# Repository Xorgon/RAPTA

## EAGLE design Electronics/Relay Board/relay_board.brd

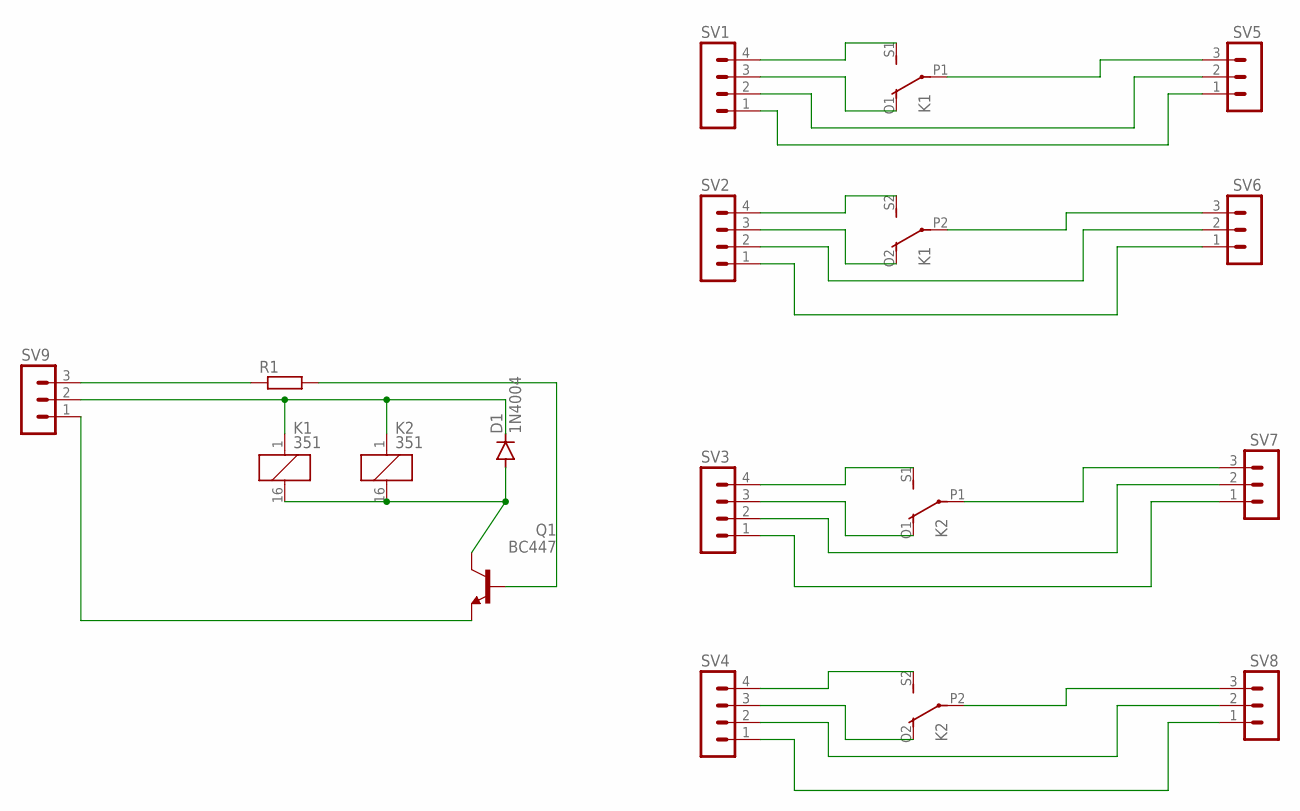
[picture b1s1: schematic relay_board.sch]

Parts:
D1: 1N4004; DO41-10
K1, K2: 351
Q1: BC447; TO92-EBC
R1: R-EU_0207/15; 0207/15
SV1, SV2, SV3, SV4: MA04-1
SV5, SV6, SV7, SV8, SV9: MA03-1

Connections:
unnamed: K1.O1 (O), SV1.3
unnamed: K1.S1 (S), SV1.4
unnamed: K1.S2 (S), SV2.4
unnamed: K1.O2 (O), SV2.3
unnamed: K2.S1 (S), SV3.4
unnamed: K2.O1 (O), SV3.3
unnamed: K2.S2 (S), SV4.4
unnamed: K2.O2 (O), SV4.3
unnamed: K1.P1, SV5.3
unnamed: SV1.1, SV5.1
unnamed: SV1.2, SV5.2
unnamed: K1.P2, SV6.3
unnamed: SV2.2, SV6.2
unnamed: SV2.1, SV6.1
unnamed: K2.P1, SV7.3
unnamed: K2.P2, SV8.3
unnamed: SV3.2, SV7.2
unnamed: SV3.1, SV7.1
unnamed: SV4.2, SV8.2
unnamed: SV4.1, SV8.1
unnamed: D1.C, K1.1, K2.1, SV9.2
unnamed: D1.A, K1.16 (2), K2.16 (2), Q1.C
unnamed: Q1.E, SV9.1
unnamed: R1.1, SV9.3
unnamed: Q1.B, R1.2

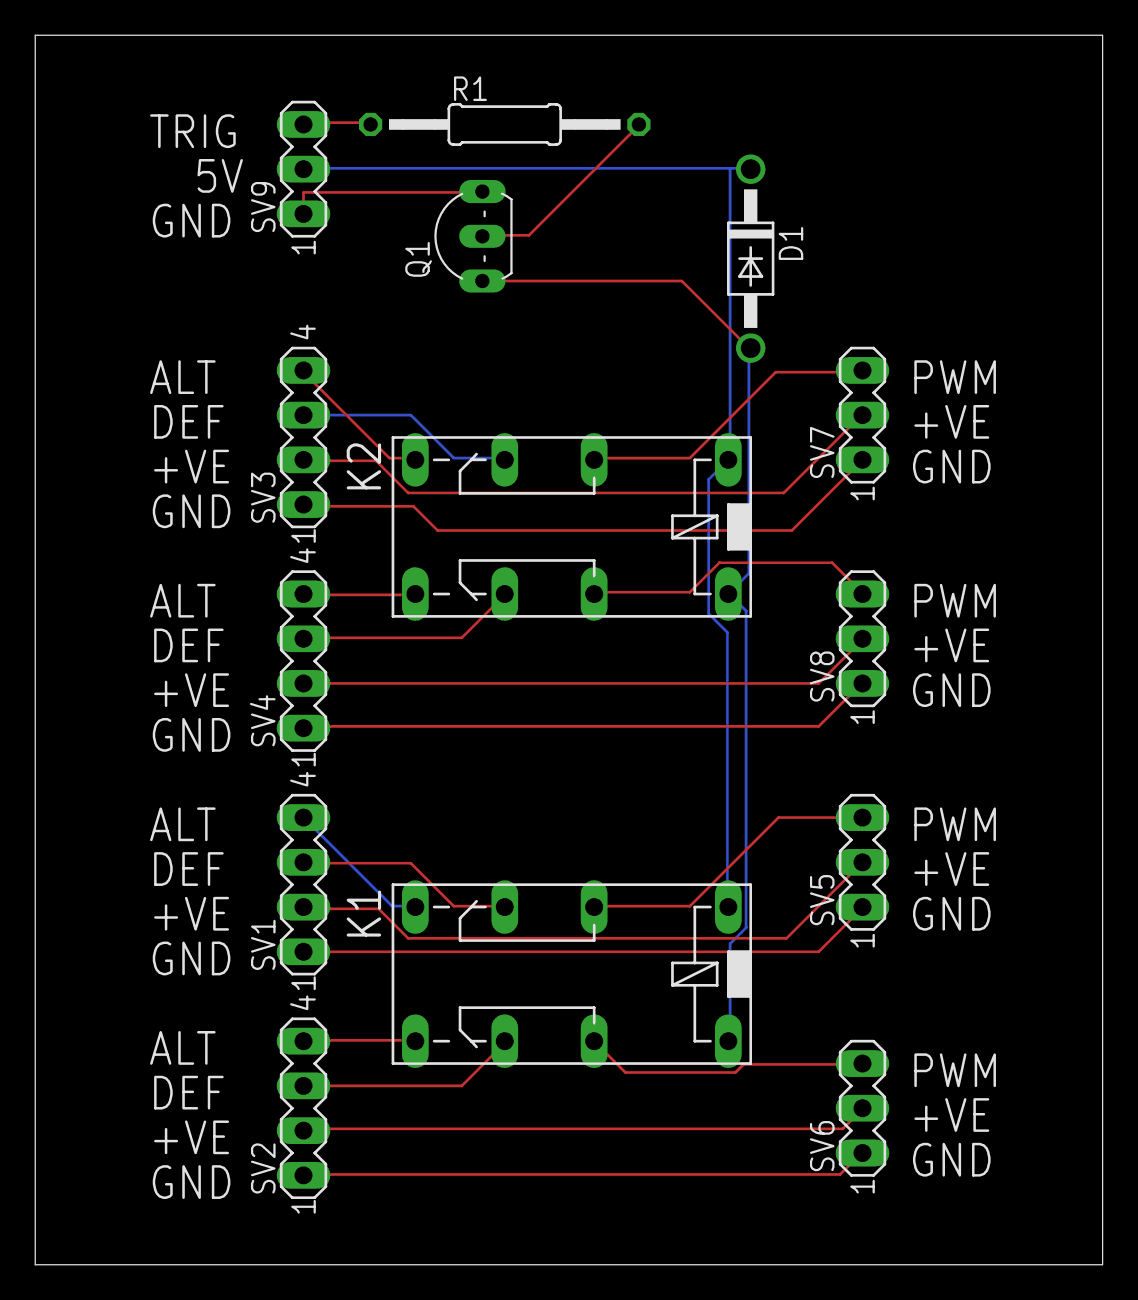
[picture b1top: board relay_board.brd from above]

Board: 2 copper layers, 60.6 x 69.8 mm, 14 parts (0 on the bottom side), 25 nets.

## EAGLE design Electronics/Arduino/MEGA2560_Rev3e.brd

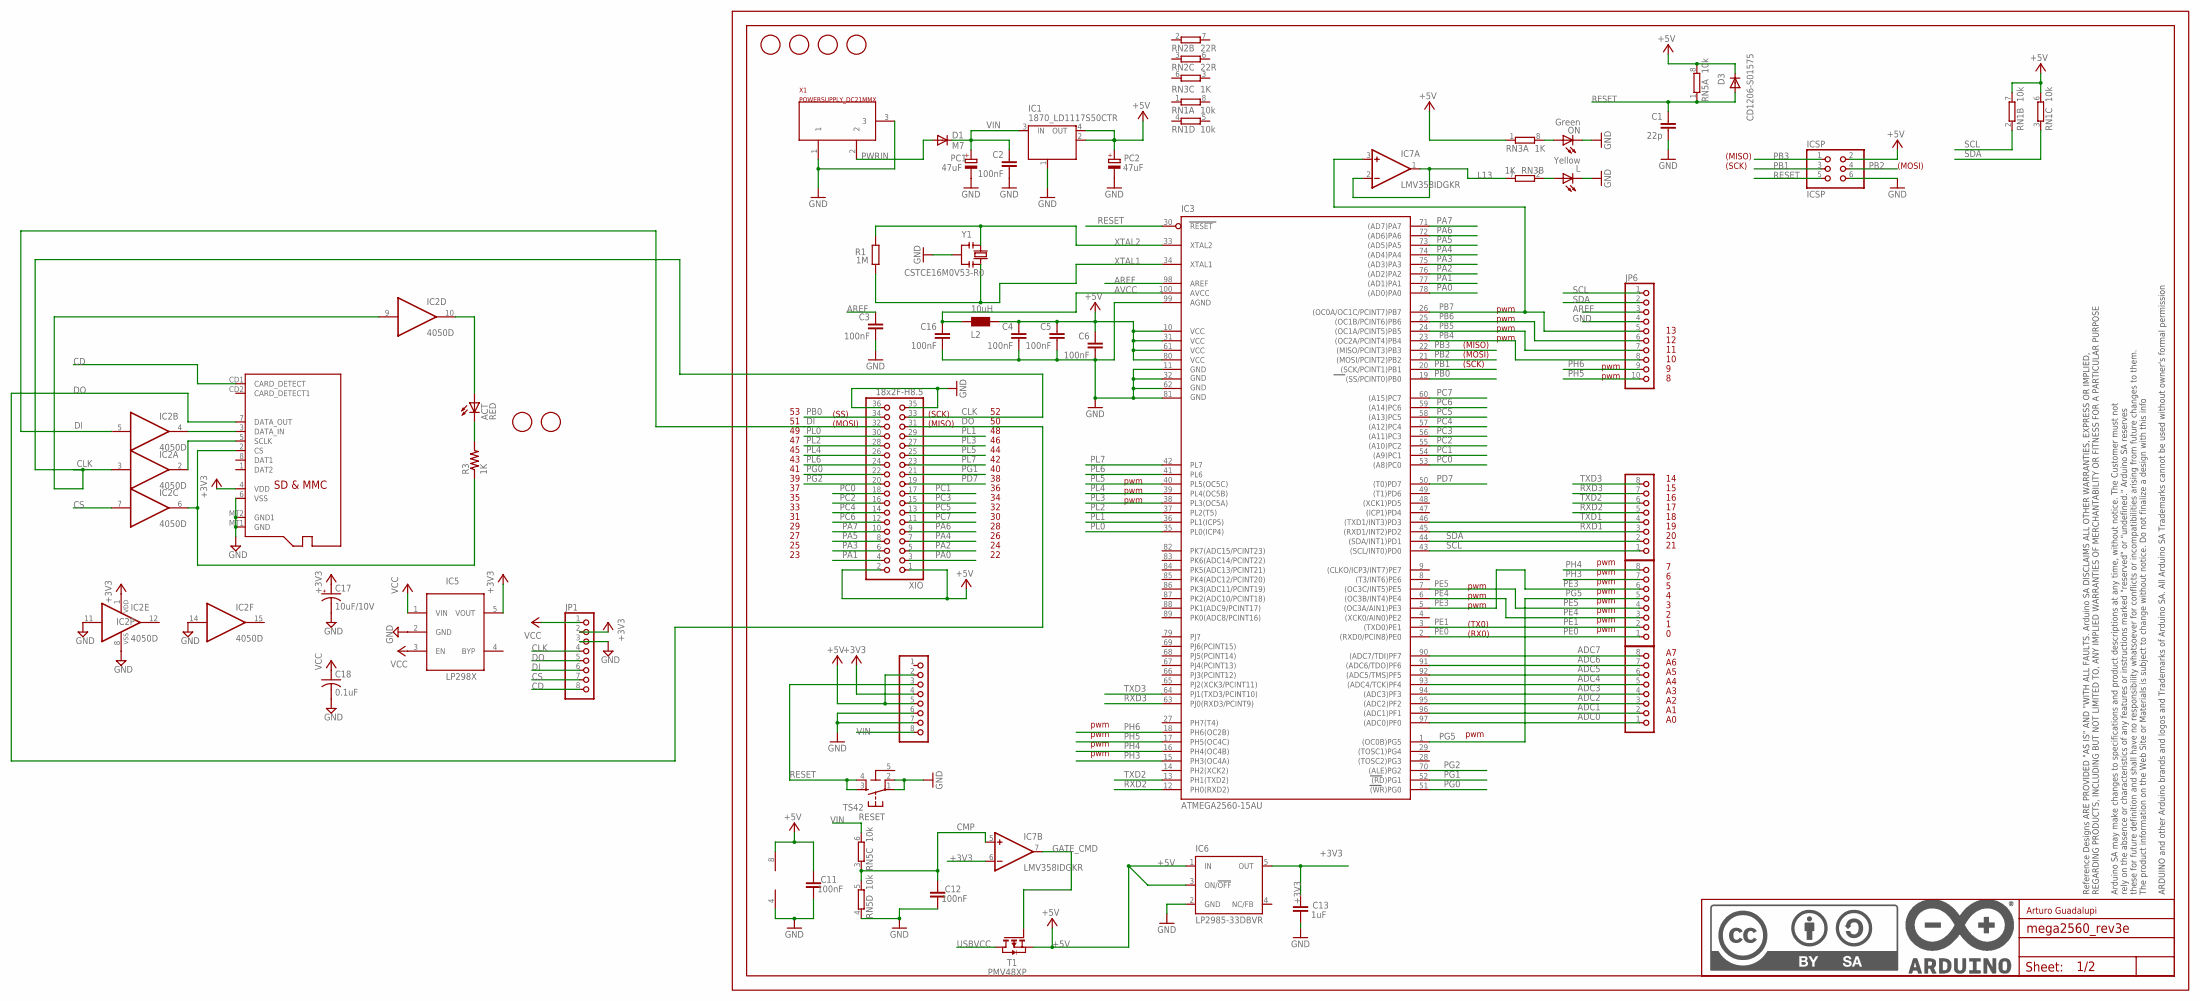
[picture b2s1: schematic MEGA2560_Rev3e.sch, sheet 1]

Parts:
ACT: RED; CHIP-LED0805
ADCL: FH254-108DF08500V; 1X08
C1: 22p; C0603-ROUND
C2, C3, C4, C5, C6, C11, C12, C16: 100nF; C0603-ROUND
C13: 1uF; C0603-ROUND
C17: 10uF/10V; A/3216-18R
C18: 0.1uF; C0805K
COMMUNICATION: FH254-108DF08500V; 1X08
D1: M7; SMB
D3: CD1206-S01575; MINIMELF
FD1, FD2, FD3, FD4: FIDUCIALMOUNT; FIDUCIA-MOUNT
IC1: 1870_LD1117S50CTR; LINEAR_SOT223
IC2: 4050D; SO16
IC3: ATMEGA2560-15AU; TQFP100
IC5: LP298XS; SOT23-5L
IC6: LP2985-33DBVR; SOT23-DBV
IC7: LMV358IDGKR; MSOP08
ICSP: ICSP; 2X03
JP1: PINHD-1X8BIG; 1X08-BIG
JP6: FH254-110DF08500V; 1X10
L: Yellow; CHIPLED_0805
L2: 10uH; 0805
ON: Green; CHIPLED_0805
PC1, PC2: 47uF; PANASONIC_D
POWER: FH254-108DF08500V; 1X08
PWML: FH254-108DF08500V; 1X08
R1: 1M; R0603-ROUND
R3: 1K; R0805
RESET: TS42
RN1, RN5: 10k; CAY16
RN2: 22R; CAY16
RN3: 1K; CAY16
T1: PMV48XP; SOT-23; PART_NUMBER PMV48XP
U$1: DNP; FRAME
U$3, U$4: FIDUCIAL; FIDUCIAL_1MM
X1: POWERSUPPLY_DC21MMX; POWERSUPPLY_DC-21MM
X3: MICROSD
XIO: 18x2F-H8.5; 2X18
Y1: CSTCE16M0V53-R0; RESONATOR

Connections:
5-GND: RESET.5 (5-GND)
+3V3: C13.2, C17.+, IC2.1 (VDD), IC5.5 (VOUT), IC6.5 (OUT), IC7.6 (-IN), JP1.2, POWER.4, X3.4 (VDD)
+5V: C4.1, C5.1, C6.1, C11.2, D3.C, IC1.2 (OUT), IC1.4 (OUT), IC3.10 (VCC), IC3.31 (VCC1), IC3.61 (VCC2), IC3.80 (VCC3), IC6.1 (IN), IC6.3 (ON/!OFF), IC7.8 (V+), ICSP.2, L2.2, PC2.+, POWER.2, POWER.5, RN1.6 (2), RN1.7 (2), RN3.1, RN5.8 (2), T1.2 (S), XIO.1, XIO.2; also elsewhere on the board
ADC0: ADCL.1, IC3.97 ((ADC0)PF0)
ADC1: ADCL.2, IC3.96 ((ADC1)PF1)
ADC2: ADCL.3, IC3.95 ((ADC2)PF2)
ADC3: ADCL.4, IC3.94 ((ADC3)PF3)
ADC4: ADCL.5, IC3.93 ((ADC4/TCK)PF4)
ADC5: ADCL.6, IC3.92 ((ADC5/TMS)PF5)
ADC6: ADCL.7, IC3.91 ((ADC6/TDO)PF6)
ADC7: ADCL.8, IC3.90 ((ADC7/TDI)PF7)
AREF: C3.1, IC3.98 (AREF), JP6.3
AVCC: C16.1, IC3.100 (AVCC), L2.1
CD: JP1.8, X3.CD1 (CARD_DETECT)
CLK: IC2.3 (I), IC2.9 (I), JP1.4, XIO.33
CMP: C12.2, IC7.5 (+IN), RN5.3 (1), RN5.5 (2)
CS: IC2.7 (I), JP1.7
DI: IC2.5 (I), JP1.6, XIO.32
DO: JP1.5, X3.7 (DATA_OUT), XIO.31
GATE_CMD: IC7.7 (OUT), T1.3 (G)
GND: C1.2, C2.2, C3.2, C4.2, C5.2, C6.2, C11.1, C12.1, C13.1, C16.2, C17.-, C18.2, IC1.1 (GND/ADJ), IC2.8 (VSS), IC2.11 (I), IC2.14 (I), IC3.11 (GND), IC3.32 (GND1), IC3.62 (GND2), IC3.81 (GND3), IC3.99 (AGND), IC5.2 (GND), IC6.2 (GND), IC7.4 (V-), ICSP.6, JP1.3, JP6.4, L.C, ON.C, PC1.-, PC2.-, POWER.6, POWER.7, RESET.1, RESET.2, RN5.4 (1), X1.1, X1.3, X3.6 (VSS), X3.MT1 (GND), X3.MT2 (GND1), XIO.35, XIO.36, Y1.2; also elsewhere on the board
L13: IC7.1 (OUT), IC7.2 (-IN), RN3.7 (2)
unnamed: ACT.A, IC2.10 (O)
unnamed: L.A, RN3.2 (1)
unnamed: ON.A, RN3.8 (2)
unnamed: IC2.2 (O), X3.5 (SCLK)
unnamed: IC2.6 (O), R3.1, X3.2 (CS)
unnamed: ACT.C, R3.2
unnamed: IC2.4 (O), X3.3 (DATA_IN)
PA0: IC3.78 ((AD0)PA0), XIO.3
PA1: IC3.77 ((AD1)PA1), XIO.4
PA2: IC3.76 ((AD2)PA2), XIO.5
PA3: IC3.75 ((AD3)PA3), XIO.6
PA4: IC3.74 ((AD4)PA4), XIO.7
PA5: IC3.73 ((AD5)PA5), XIO.8
PA6: IC3.72 ((AD6)PA6), XIO.9
PA7: IC3.71 ((AD7)PA7), XIO.10
PB0: IC3.19 ((SS/PCINT0)PB0), XIO.34
PB1: IC3.20 ((SCK/PCINT1)PB1), ICSP.3
PB2: IC3.21 ((MOSI/PCINT2)PB2), ICSP.4
PB3: IC3.22 ((MISO/PCINT3)PB3), ICSP.1
PB4: IC3.23 ((OC2A/PCINT4)PB4), JP6.8
PB5: IC3.24 ((OC1A/PCINT5)PB5), JP6.7
PB6: IC3.25 ((OC1B/PCINT6)PB6), JP6.6
PB7: IC3.26 ((OC0A/OC1C/PCINT7)PB7), IC7.3 (+IN), JP6.5
PC0: IC3.53 ((A8)PC0), XIO.18
PC1: IC3.54 ((A9)PC1), XIO.17
PC2: IC3.55 ((A10)PC2), XIO.16
PC3: IC3.56 ((A11)PC3), XIO.15
PC4: IC3.57 ((A12)PC4), XIO.14
PC5: IC3.58 ((A13)PC5), XIO.13
PC6: IC3.59 ((A14)PC6), XIO.12
PC7: IC3.60 ((A15)PC7), XIO.11
PD7: IC3.50 ((T0)PD7), XIO.19
PE0: IC3.2 ((RXD0/PCIN8)PE0), PWML.1; also elsewhere on the board
PE1: IC3.3 ((TXD0)PE1), PWML.2; also elsewhere on the board
PE3: IC3.5 ((OC3A/AIN1)PE3), PWML.6
PE4: IC3.6 ((OC3B/INT4)PE4), PWML.3
PE5: IC3.7 ((OC3C/INT5)PE5), PWML.4
PG0: IC3.51 ((WR)PG0), XIO.22
PG1: IC3.52 ((RD)PG1), XIO.21
PG2: IC3.70 ((ALE)PG2), XIO.20
PG5: IC3.1 ((OC0B)PG5), PWML.5
PH3: IC3.15 (PH3(OC4A)), PWML.7
PH4: IC3.16 (PH4(OC4B)), PWML.8
PH5: IC3.17 (PH5(OC4C)), JP6.10
PH6: IC3.18 (PH6(OC2B)), JP6.9
PL0: IC3.35 (PL0(ICP4)), XIO.30
PL1: IC3.36 (PL1(ICP5)), XIO.29
PL2: IC3.37 (PL2(T5)), XIO.28
PL3: IC3.38 (PL3(OC5A)), XIO.27
PL4: IC3.39 (PL4(OC5B)), XIO.26
PL5: IC3.40 (PL5(OC5C)), XIO.25
PL6: IC3.41 (PL6), XIO.24
PL7: IC3.42 (PL7), XIO.23
PWRIN: D1.A, X1.2
RESET: C1.1, D3.A, IC3.30 (RESET), ICSP.5, POWER.3, RESET.3, RESET.4, RN5.1; also elsewhere on the board
RXD1: COMMUNICATION.3, IC3.45 ((RXD1/INT2)PD2)
RXD2: COMMUNICATION.5, IC3.12 (PH0(RXD2))
RXD3: COMMUNICATION.7, IC3.63 (PJ0(RXD3/PCINT9))
SCL: COMMUNICATION.1, IC3.43 ((SCL/INT0)PD0), JP6.1, RN1.2 (1)
SDA: COMMUNICATION.2, IC3.44 ((SDA/INT1)PD1), JP6.2, RN1.3 (1)
TXD1: COMMUNICATION.4, IC3.46 ((TXD1/INT3)PD3)
TXD2: COMMUNICATION.6, IC3.13 (PH1(TXD2))
TXD3: COMMUNICATION.8, IC3.64 (PJ1(TXD3/PCINT10))
USBVCC: T1.1 (D); also elsewhere on the board
VCC: C18.1, IC5.1 (VIN), IC5.3 (EN), JP1.1
VIN: C2.1, D1.C, IC1.3 (IN), PC1.+, POWER.8, RN5.6 (2)
XTAL1: IC3.34 (XTAL1), R1.1, Y1.3
XTAL2: IC3.33 (XTAL2), R1.2, Y1.1

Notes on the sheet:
(SCK)
(MISO)
(MOSI)
pwm
(TX0)
(RX0)
(SS)
Arturo Guadalupi

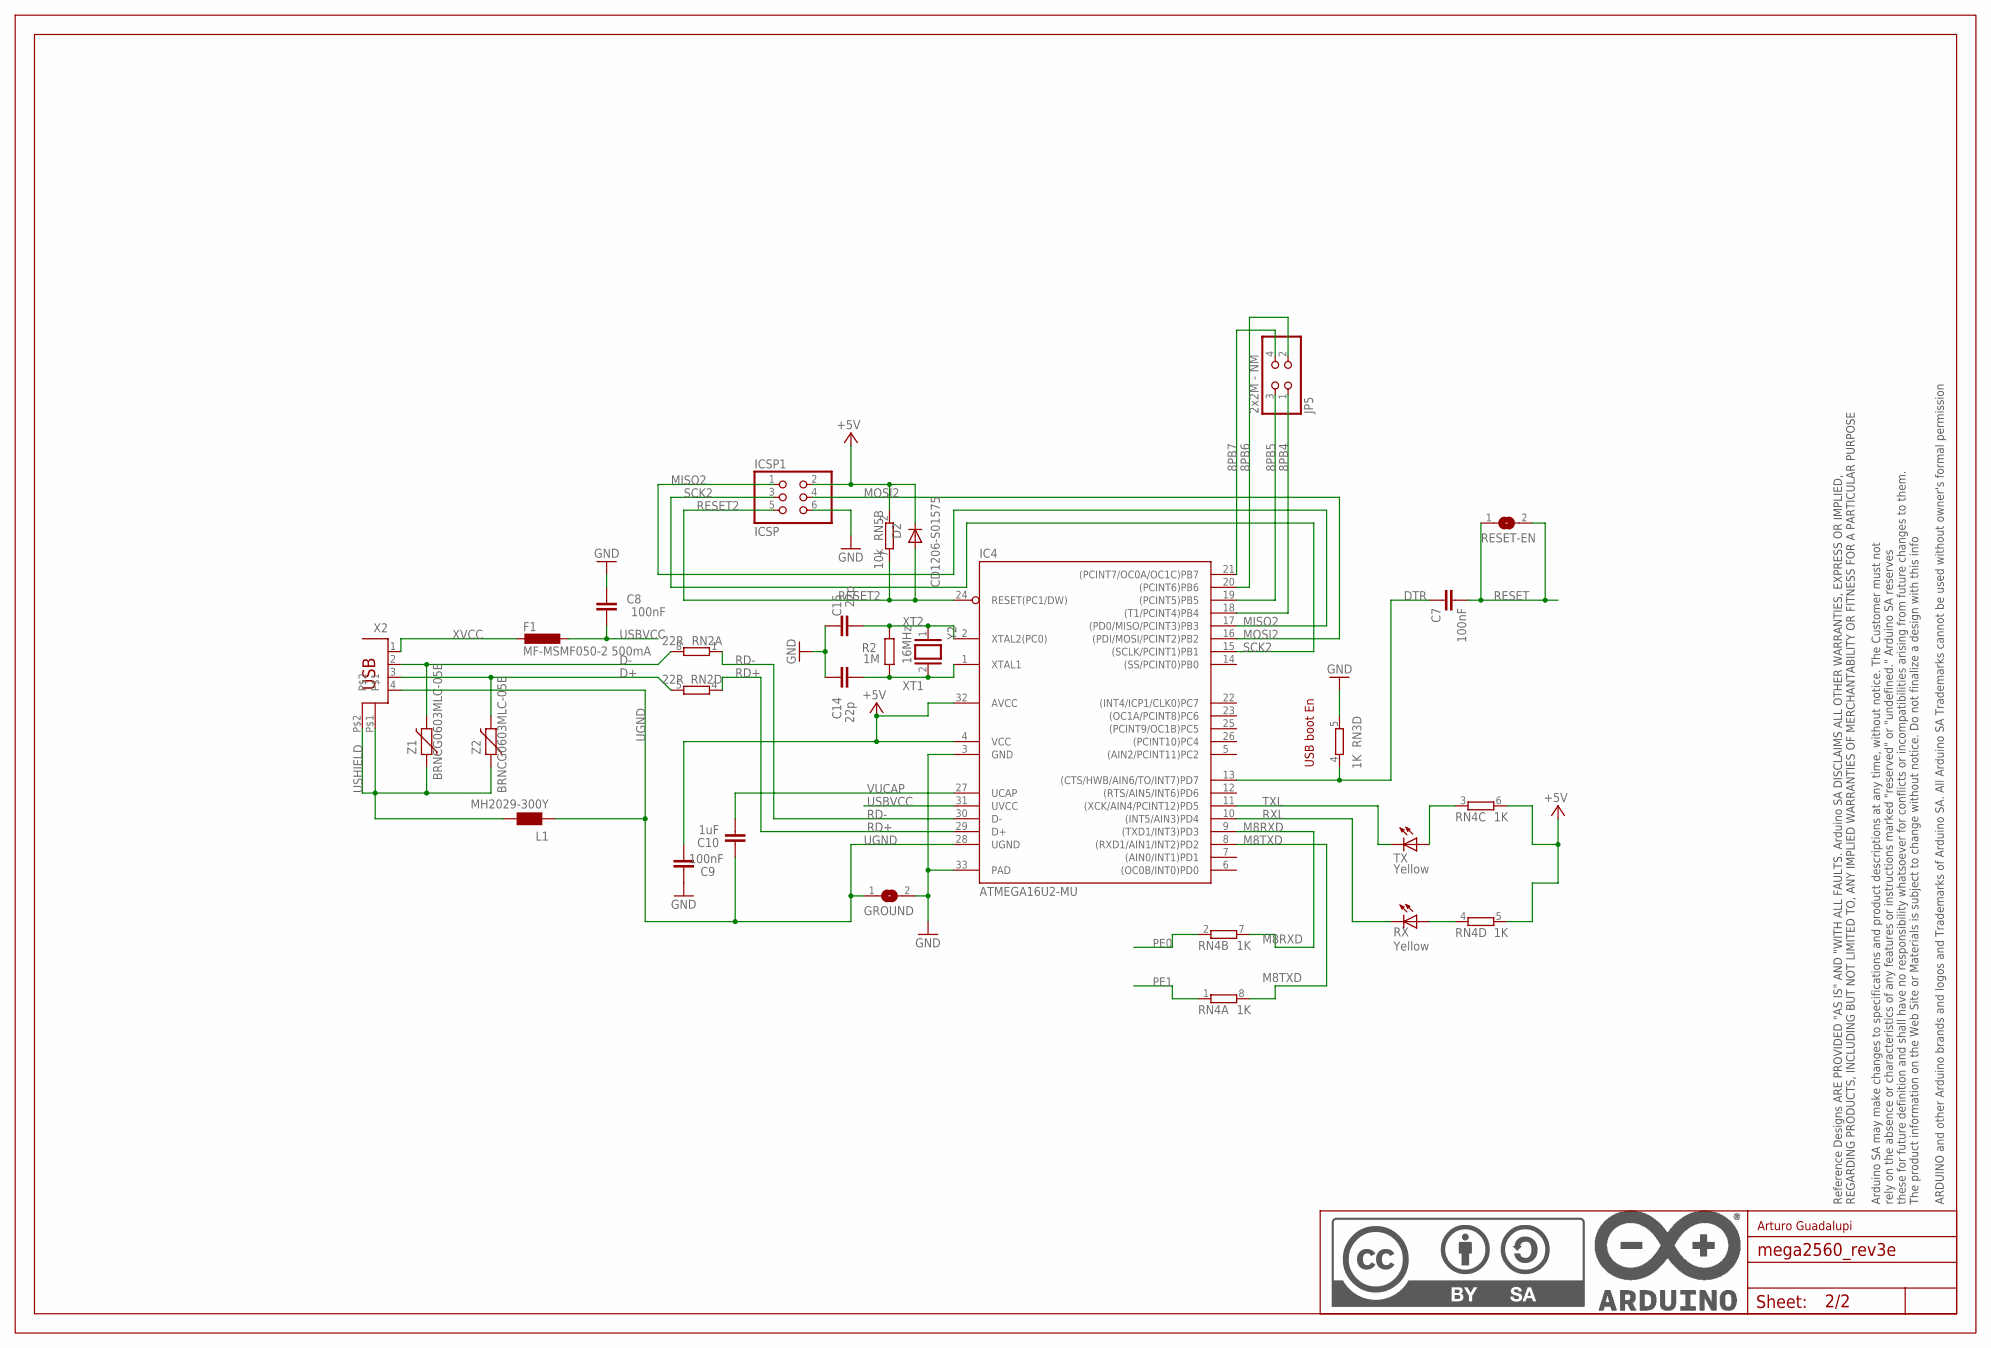
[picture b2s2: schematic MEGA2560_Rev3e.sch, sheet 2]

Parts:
C7, C8, C9: 100nF; C0603-ROUND
C10: 1uF; C0603-ROUND
C14, C15: 22p; C0603-ROUND
D2: CD1206-S01575; MINIMELF
F1: MF-MSMF050-2 500mA; L1812
GROUND: SJ
IC4: ATMEGA16U2-MU; MLF32
ICSP1: ICSP; 2X03
JP5: 2x2M - NM; 2X02
L1: MH2029-300Y; 0805
R2: 1M; R0603-ROUND
RESET-EN: SJ
RN2: 22R; CAY16
RN3, RN4: 1K; CAY16
RN5: 10k; CAY16
RX: Yellow; CHIPLED_0805
TX: Yellow; CHIPLED_0805
U$2: DNP; FRAME
X2: 0056_USB-B-S-RA-WT-SPCC; PN61729
Y2: 16MHz; QS
Z1, Z2: BRNCG0603MLC-05E; CT/CN0603

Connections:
8PB4: IC4.18 ((T1/PCINT4)PB4), JP5.1
8PB5: IC4.19 ((PCINT5)PB5), JP5.3
8PB6: IC4.20 ((PCINT6)PB6), JP5.2
8PB7: IC4.21 ((PCINT7/OC0A/OC1C)PB7), JP5.4
+5V: C9.1, D2.C, IC4.4 (VCC), IC4.32 (AVCC), ICSP1.2, RN4.5 (2), RN4.6 (2), RN5.2 (1); also elsewhere on the board
D+: RN2.5 (2), X2.3, Z2.2
D-: RN2.8 (2), X2.2, Z1.2
DTR: C7.1, IC4.13 ((CTS/HWB/AIN6/TO/INT7)PD7), RN3.4 (1)
GND: C8.2, C9.2, C14.2, C15.2, GROUND.2, IC4.3 (GND), IC4.33 (PAD), ICSP1.6, RN3.5 (2); also elsewhere on the board
M8RXD: IC4.9 ((TXD1/INT3)PD3), RN4.7 (2)
M8TXD: IC4.8 ((RXD1/AIN1/INT2)PD2), RN4.8 (2)
MISO2: IC4.17 ((PD0/MISO/PCINT3)PB3), ICSP1.1
MOSI2: IC4.16 ((PDI/MOSI/PCINT2)PB2), ICSP1.4
unnamed: RN4.4 (1), RX.A
unnamed: RN4.3 (1), TX.A
PE0: RN4.2 (1); also elsewhere on the board
PE1: RN4.1; also elsewhere on the board
RD+: IC4.29 (D+), RN2.4 (1)
RD-: IC4.30 (D-), RN2.1
RESET: C7.2, RESET-EN.1, RESET-EN.2; also elsewhere on the board
RESET2: D2.A, IC4.24 (RESET(PC1/DW)), ICSP1.5, RN5.7 (2)
RXL: IC4.10 ((INT5/AIN3)PD4), RX.C
SCK2: IC4.15 ((SCLK/PCINT1)PB1), ICSP1.3
TXL: IC4.11 ((XCK/AIN4/PCINT12)PD5), TX.C
UGND: C10.2, GROUND.1, IC4.28 (UGND), L1.1, X2.4
USBVCC: C8.1, F1.1, IC4.31 (UVCC); also elsewhere on the board
USHIELD: L1.2, X2.P$1, X2.P$2, Z1.1, Z2.1
VUCAP: C10.1, IC4.27 (UCAP)
XT1: C14.1, IC4.1 (XTAL1), R2.1, Y2.2
XT2: C15.1, IC4.2 (XTAL2(PC0)), R2.2, Y2.1
XVCC: F1.2, X2.1

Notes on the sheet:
USB boot En
Arturo Guadalupi

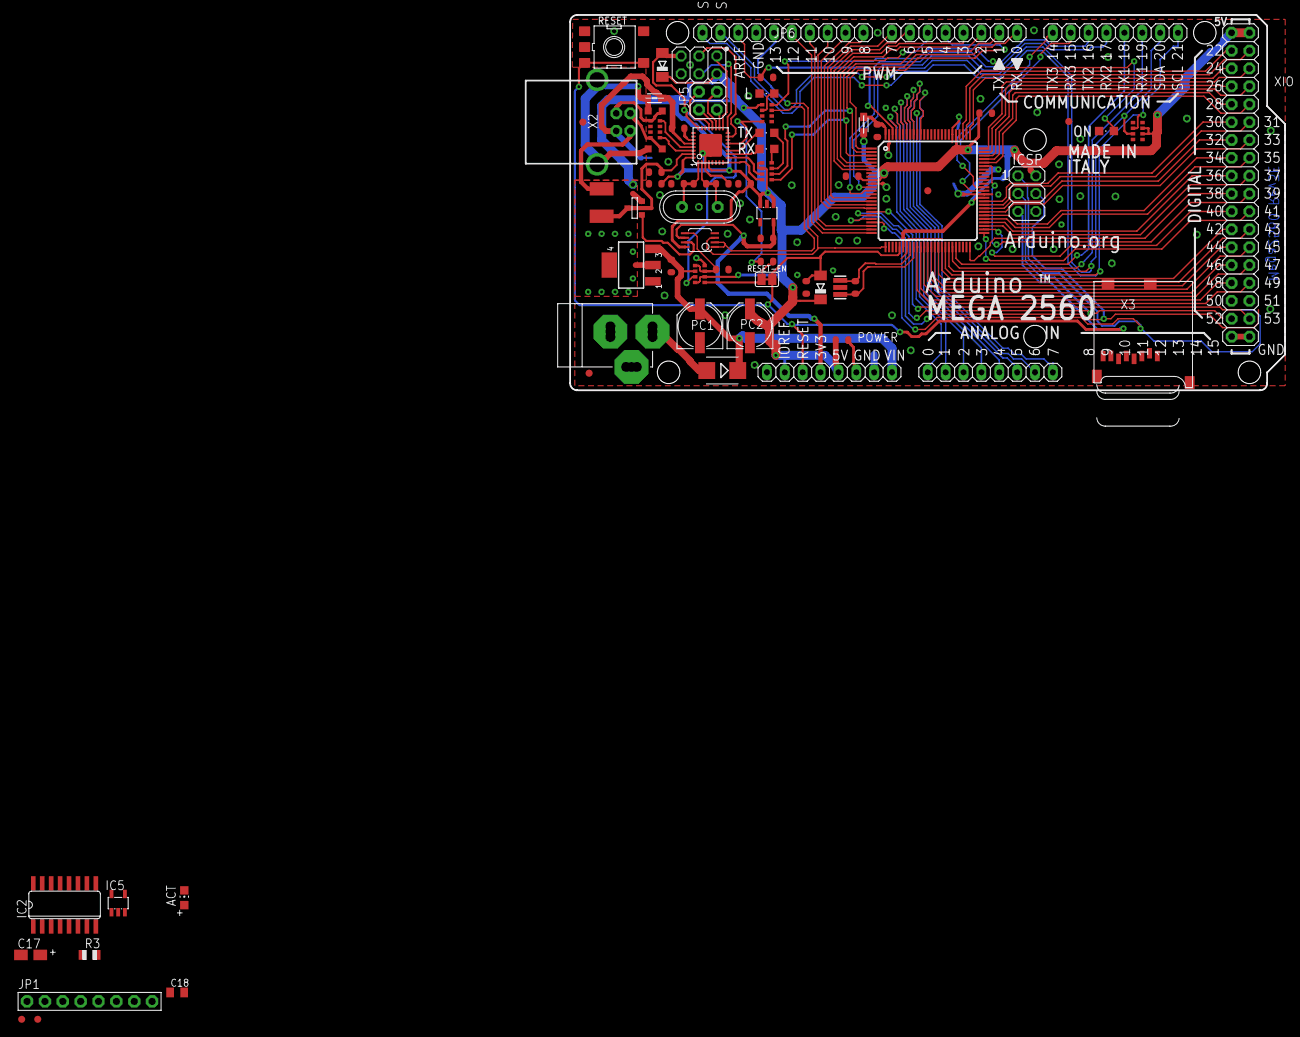
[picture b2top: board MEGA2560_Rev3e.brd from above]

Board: 2 copper layers, 101.6 x 53.3 mm, 75 parts (1 on the bottom side), 114 nets.

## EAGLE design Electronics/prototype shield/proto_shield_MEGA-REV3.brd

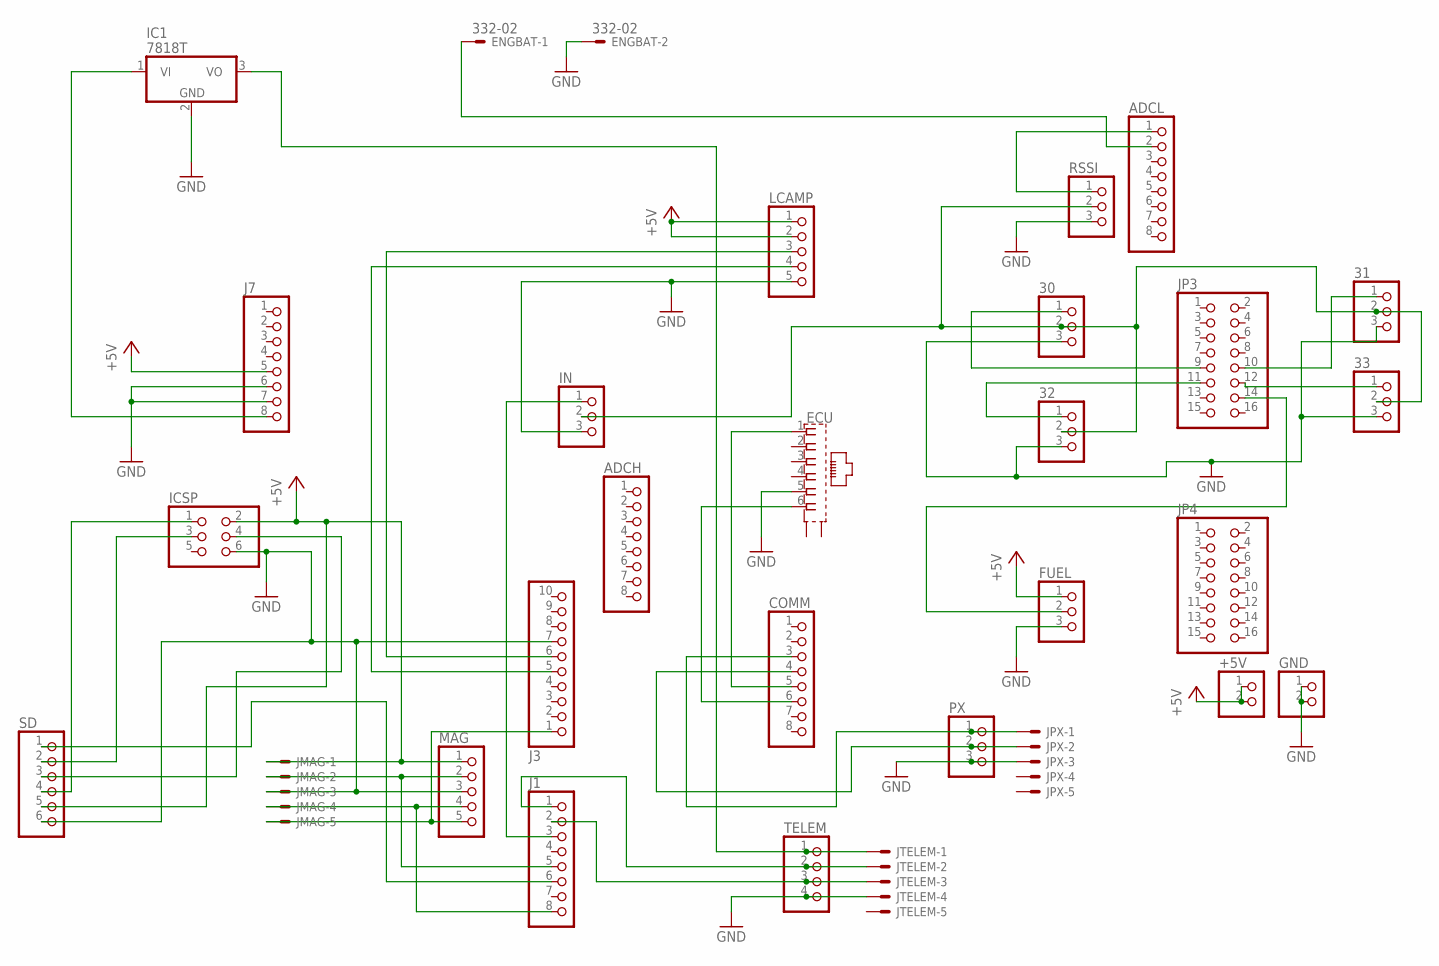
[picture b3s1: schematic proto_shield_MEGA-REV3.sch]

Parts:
30, 31, 32, 33: PINHD-1X3; 1X03
+5V: PINHD-1X2; 1X02
ADCH: PINHD-1X8TH; 1X08-TH
ADCL: PINHD-1X8TH; 1X08-TH
COMM: PINHD-1X8TH; 1X08-TH
ECU: XRJK-S-01-6-6-0-2G2-NO
ENGBAT: 332-02
FUEL: PINHD-1X3; 1X03
GND: PINHD-1X2; 1X02
IC1: 7818T; TO220H
ICSP: PINHD-2X3; 2X03
IN: PINHD-1X3; 1X03
J1, J7: PINHD-1X8TH; 1X08-TH
J3: PINHD-1X10TH; 1X10-TH
JMAG: BM05B-SRSS-TB
JP3, JP4: PINHD-2X8; 2X08
JPX: BM05B-SRSS-TB
JTELEM: BM05B-SRSS-TB
LCAMP: PINHD-1X5; 1X05
MAG: PINHD-1X5; 1X05
PX: PINHD-1X3; 1X03
RSSI: PINHD-1X3; 1X03
SD: PINHD-1X6; 1X06
TELEM: PINHD-1X4; 1X04

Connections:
+5V: +5V.1, +5V.2, FUEL.1, ICSP.2, J7.5, JMAG.1, LCAMP.1, LCAMP.2, MAG.1, SD.5
GND: 30.3, 31.3, 32.3, 33.3, ECU.5, ENGBAT.2, FUEL.3, GND.1, GND.2, IC1.2 (GND), ICSP.6, IN.3, J3.7, J7.6, J7.7, JMAG.3, JPX.3, JTELEM.4, LCAMP.5, MAG.3, PX.3, RSSI.3, SD.6, TELEM.4
unnamed: COMM.5, ECU.1
unnamed: COMM.6, ECU.6
unnamed: J3.6, LCAMP.3
unnamed: J3.5, LCAMP.4
unnamed: J1.6, SD.1
unnamed: ICSP.4, SD.3
unnamed: ICSP.3, SD.2
unnamed: ICSP.1, SD.4
unnamed: J1.5, JMAG.2, MAG.2
unnamed: J1.8, JMAG.4, MAG.4
unnamed: J3.1, JMAG.5, MAG.5
unnamed: IN.1, J1.3
unnamed: ADCL.1, RSSI.1
unnamed: ADCL.2, ENGBAT.1
unnamed: 31.1, JP3.10
unnamed: 33.1, JP3.12
unnamed: 32.1, JP3.11
unnamed: 30.1, JP3.9
unnamed: COMM.3, JPX.1, PX.1
unnamed: COMM.4, JPX.2, PX.2
unnamed: J1.1, JTELEM.2, TELEM.2
unnamed: J1.2, JTELEM.3, TELEM.3
unnamed: FUEL.2, JP3.14
unnamed: IC1.3 (VO), JTELEM.1, TELEM.1
unnamed: IC1.1 (VI), J7.8
unnamed: 30.2, 31.2, 32.2, 33.2, IN.2, RSSI.2

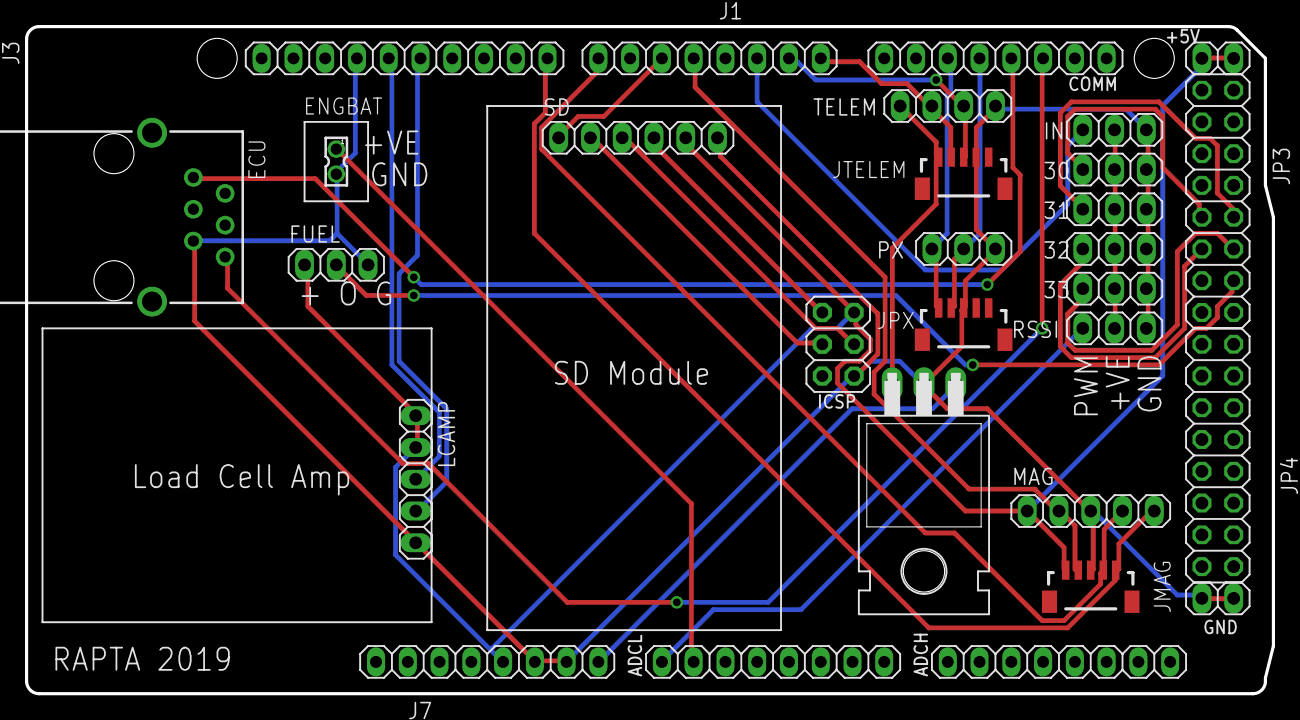
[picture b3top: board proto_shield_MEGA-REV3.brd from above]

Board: 2 copper layers, 99.7 x 53.3 mm, 29 parts (0 on the bottom side), 28 nets.

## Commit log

2018-12-01 Change TestECU to use hardware serial.
2018-12-01 Improved robustness of ECU code.
2018-12-02 Testing and debugging.
2018-12-21 Added mavlink to libraries.
2018-12-21 Added debug message to ECU.
2018-12-21 Added Pixhawk comms code.
2018-12-21 Added AoA sensor code.
2018-12-21 Added more access functions.
2018-12-22 Added offset to allow AoA to be zeroed correctly.
2018-12-29 Fixed and improved ECU code.
2018-12-30 Improved robustness and efficiency of ECU code.
2018-12-30 Removed completed TODO.
2018-12-30 Improved Pixhawk comms code.
2018-12-30 Added sketch to be used on aircraft.
2018-12-30 Added files for modified Arduino core to expand Serial RX buffer.
2018-12-30 Increased PXComms communication rates.
2018-12-30 Removed unnecessary use of serialEvent2.
2018-12-30 Updated MavlinkTesting sketch.
2018-12-30 Added further data to Arduino Serial output.
2018-12-30 Fixed MagEncoder value to be between -180 and 180.
2018-12-30 Added Python GUI to show Serial data.
2018-12-31 Minor TelemGUI formatting changes.
2018-12-31 Added COM port selection for TelemGUI.
2019-01-01 Improved COM port selection in TelemGUI.
2019-02-04 Changed values to work with telemetry radios.
2019-02-04 Added basic error detection.
2019-02-07 Improved COM port selection.
2019-02-07 Added PWM reading test.
2019-02-08 Added GUIs directory.
2019-02-08 Removed AltSoftSerial support due to conflict with Servo.
2019-02-08 Updated .gitignore.
2019-02-08 Improved TestReadPWM accuracy.
2019-02-08 Added Wind Tunnel testing sketch and GUI.
2019-02-12 Minor Wind Tunnel testing changes.
2019-02-18 Added data to TelemGUI.
2019-02-18 Added HX711 to libraries.
2019-02-18 Separated different aircraft version sketches.
2019-02-18 Moved and renamed scaleADCRaw.
2019-02-18 Added battery voltage function.
2019-02-18 Updated TelemGUI.
2019-02-20 Fixed and tested load cell code.
2019-02-20 Added lag checking.
2019-02-25 Implemented logging to file.
2019-02-25 Added pxConfig.
2019-02-25 Added EDF battery reading.
2019-02-25 Added start script for TelemGUI.
2019-02-27 Added GPS to TelemGUI.
2019-02-27 Added GPS satellite count.
2019-02-27 Partial fixes for GPS status.
2019-02-27 Added load cell taring.
2019-02-27 Added telemetry logging.
2019-03-07 Added throttle PWM measurement to initial aircraft sketch.
2019-04-11 Added log parsing tools.
2019-04-11 Added various EAGLE files for PCBs.
2019-04-11 Improved graph changes.
2019-04-19 Slight rearrangement in InitialAircraft sketch.
2019-04-19 Updated RAPTASketch.ino and added new telemetry code.
2019-04-19 Modified TelemGUI to use binary data.
2019-04-19 Added scaled IMU message to PXComms.
2019-04-20 Updated flight sketch.
2019-04-20 Added further log graphs.
2019-04-20 Updated modules.
2019-04-24 Telemetry bug fixing.
2019-04-25 Minor telemetry updates.
2019-04-26 Added pitch to telemetry.
2019-04-26 More graphs.
2019-04-26 Various bug fixes.
2019-04-26 Updated load cell quotient.
2019-04-26 Corrected engine status code.
2019-04-29 Fixed drag measurement calculation.
2019-04-29 Fixed minor telemetry screen bug.
2019-04-30 Updated aircraft mass constants
2019-04-30 Added TelemGUI console debug info.
2019-05-05 Fixed logging bug.
2019-05-06 Improved telemetry and logging.
2020-11-24 Added requirements.txt for GUI applications

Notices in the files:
parts and their libraries:
Arduino-utility: Copyright (c) 2016-2017 Arduino LLC.  All right reserved.
